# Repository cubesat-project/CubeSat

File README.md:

Check out the Wiki for Project Information

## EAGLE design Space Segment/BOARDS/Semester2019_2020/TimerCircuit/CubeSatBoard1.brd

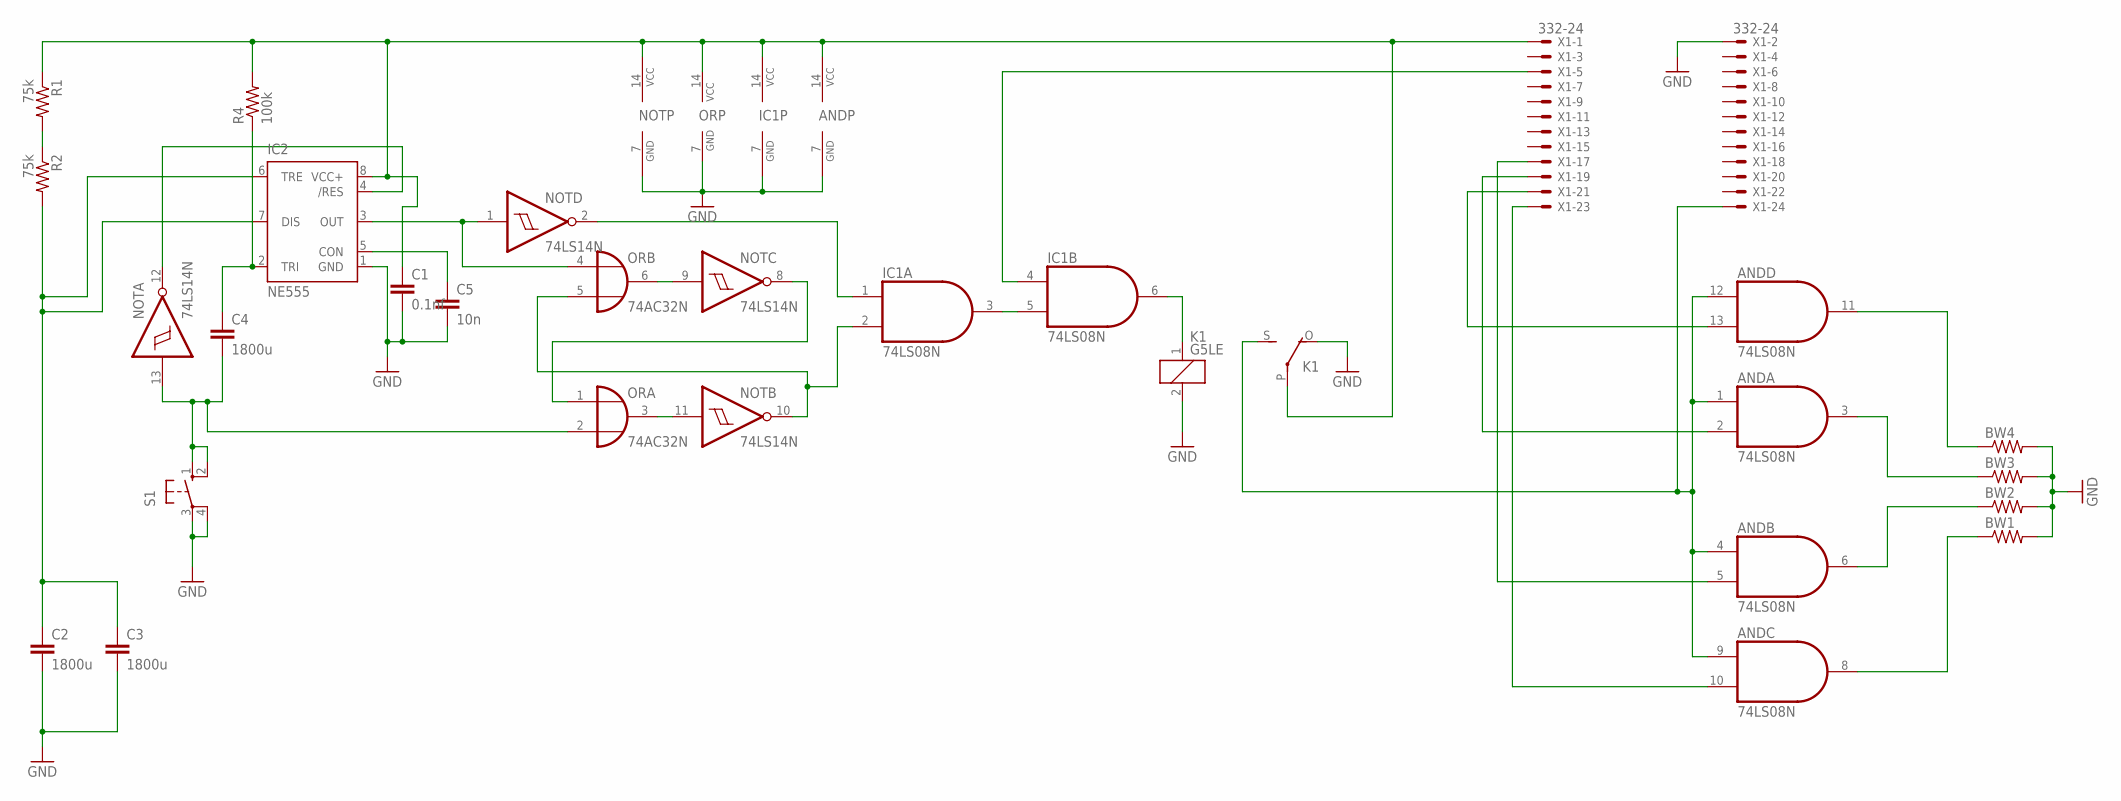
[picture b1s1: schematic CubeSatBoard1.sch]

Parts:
AND: 74LS08N; DIL14
BW1, BW2, BW3, BW4: R-US_0309/10; 0309/10
C1: 0.1nf; C5B3
C2, C3, C4: 1800u; C5B3
C5: 10n; C5B3
IC1: 74LS08N; DIL14
IC2: NE555; DIL-08
K1: G5LE
NOT: 74LS14N; DIL14
OR: 74AC32N; DIL14
R1, R2: 75k; 0309/10
R4: 100k; 0309/10
S1: 10-XX; B3F-10XX
X1: 332-24

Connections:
GND: AND.7 (GND), BW1.2, BW2.2, BW3.2, BW4.2, C1.2, C2.2, C3.2, C5.2, IC1.7 (GND), IC2.1 (GND), K1.2, K1.O, NOT.7 (GND), OR.7 (GND), S1.3, S1.4 (P1), X1.2
unnamed: R1.2, R2.1
unnamed: C2.1, C3.1, IC2.6 (TRE), IC2.7 (DIS), R2.2
unnamed: AND.14 (VCC), C1.1, IC1.14 (VCC), IC2.8 (VCC+), K1.P, NOT.14 (VCC), OR.14 (VCC), R1.1, R4.2, X1.1
unnamed: NOT.9 (I), OR.6 (O)
unnamed: IC2.4 (/RES), NOT.12 (O)
unnamed: NOT.11 (I), OR.3 (O)
unnamed: C4.2, NOT.13 (I), OR.2 (I1), S1.1 (S), S1.2 (S1)
unnamed: C4.1, IC2.2 (TRI), R4.1
unnamed: IC2.3 (OUT), NOT.1 (I), OR.4 (I0)
unnamed: C5.1, IC2.5 (CON)
unnamed: AND.13 (I1), X1.21
unnamed: NOT.8 (O), OR.1 (I0)
unnamed: IC1.2 (I1), NOT.10 (O), OR.5 (I1)
unnamed: IC1.1 (I0), NOT.2 (O)
unnamed: IC1.3 (O), IC1.5 (I1)
unnamed: AND.6 (O), BW2.1
unnamed: IC1.6 (O), K1.1
unnamed: AND.11 (O), BW4.1
unnamed: AND.3 (O), BW3.1
unnamed: AND.8 (O), BW1.1
unnamed: AND.1 (I0), AND.4 (I0), AND.9 (I0), AND.12 (I0), K1.S, X1.24
unnamed: IC1.4 (I0), X1.5
unnamed: AND.2 (I1), X1.19
unnamed: AND.5 (I1), X1.17
unnamed: AND.10 (I1), X1.23

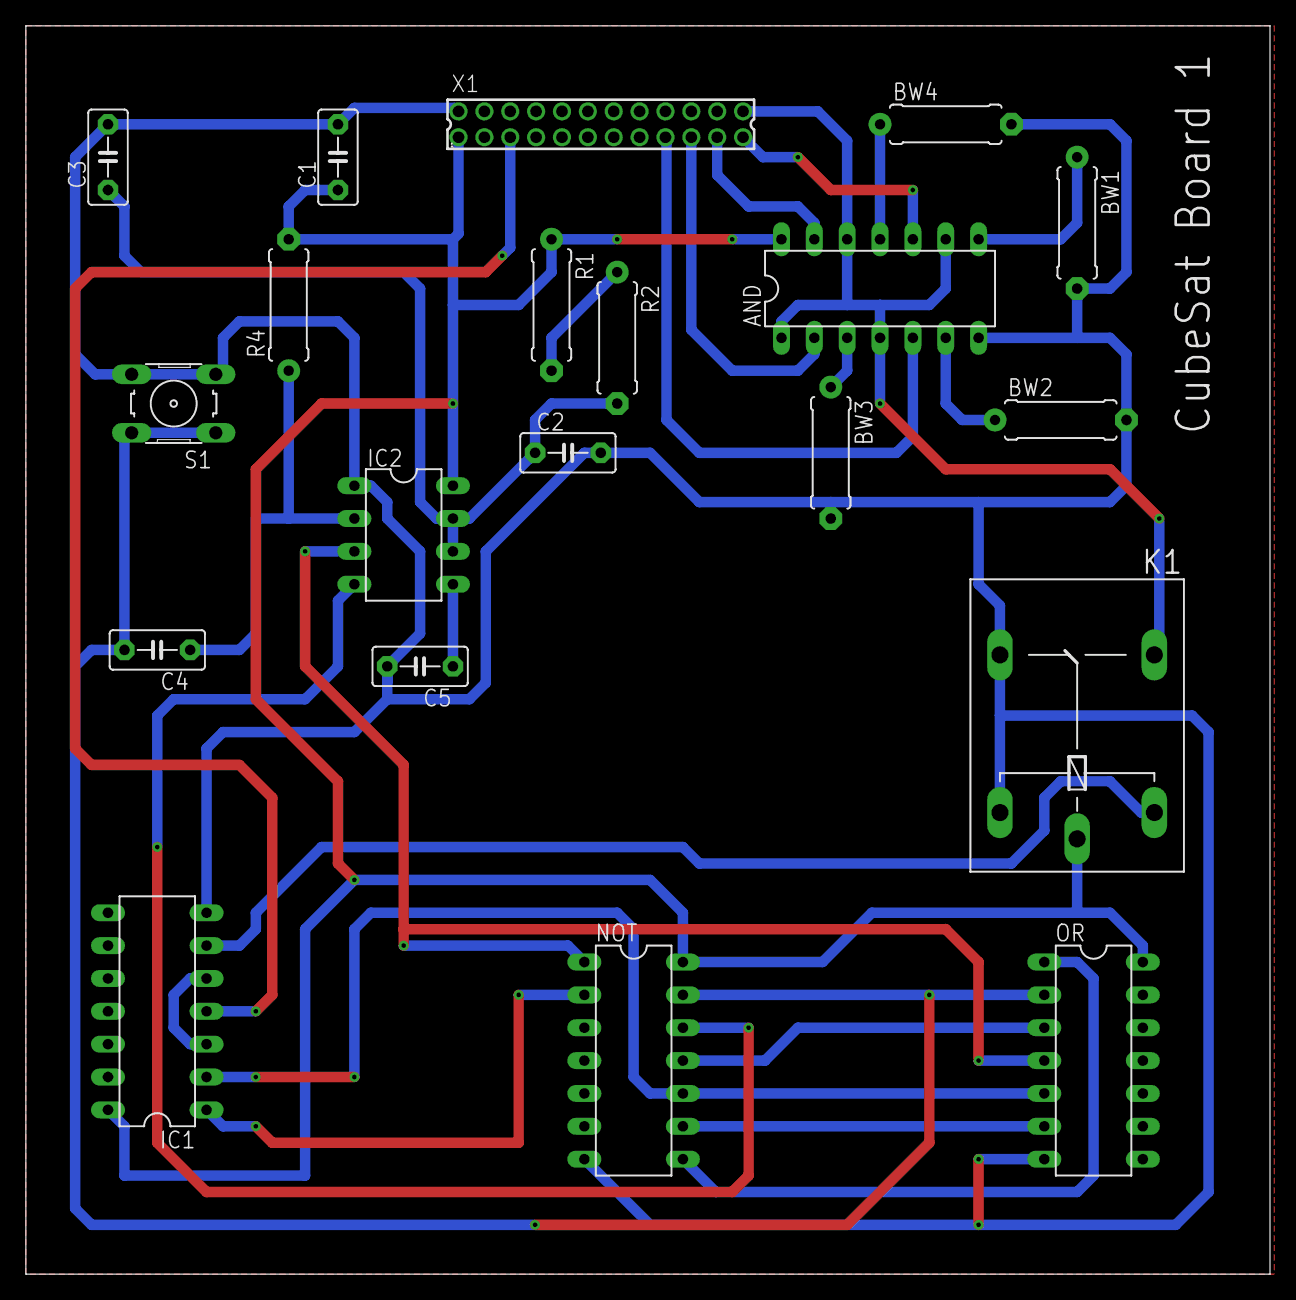
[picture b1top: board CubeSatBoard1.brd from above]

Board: 2 copper layers, 96.2 x 96.5 mm, 20 parts (0 on the bottom side), 26 nets.

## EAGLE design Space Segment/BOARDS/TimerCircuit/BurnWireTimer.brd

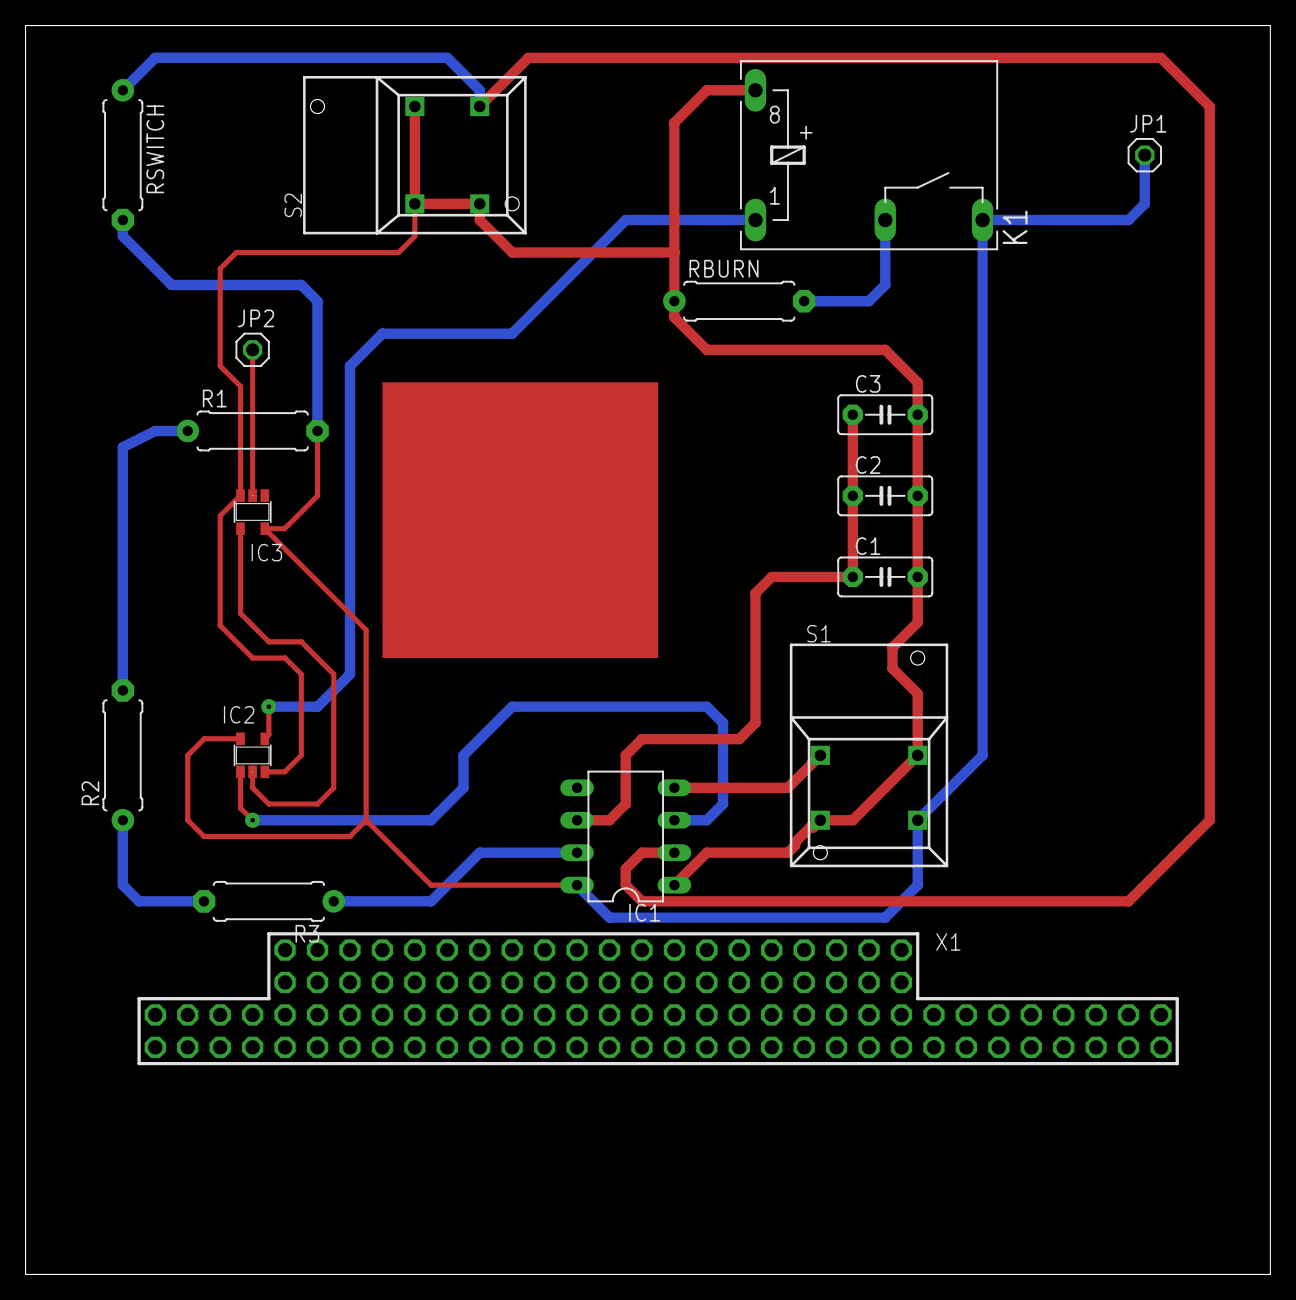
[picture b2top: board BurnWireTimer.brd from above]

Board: 2 copper layers, 97.5 x 97.8 mm, 17 parts (0 on the bottom side), 12 nets.

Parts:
C1, C2, C3: 1800u; C5B3
IC1: ICM7555; DIL08
IC2: 74AHC1G02DBV; SOT23-5
IC3: 74AHC1G04DBV; SOT23-5
JP1: 5V; 1X01
JP2: 1X01
K1: G6C-1117P
R1, R2: 132k; 0309/10
R3: 73k; 0309/10
RBURN: 4.7; 0309/10
RSWITCH: 10k; 0309/10
S1, S2: 5501
X1: 1184C

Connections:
GND: C1.2, C2.2, C3.2, IC1.1, IC2.3, IC3.3, K1.8, RBURN.1, S1.1A, S1.NC, S2.1A, S2.1B, S2.NC
unnamed: IC2.4, K1.1
unnamed: R1.1, R2.2
unnamed: R2.1, R3.2
unnamed: C1.1, C2.1, C3.1, IC1.6, IC1.7, R3.1
unnamed: IC1.4, S1.1B
unnamed: IC1.2, RSWITCH.1, S2.NO
unnamed: IC1.3, IC2.1
unnamed: IC2.2, IC3.4
unnamed: K1.P, RBURN.2
OBC: IC3.2, JP2.1
VCC: IC1.8, IC2.5, IC3.5, JP1.1, K1.S, R1.2, RSWITCH.2, S1.NO

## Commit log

2018-10-15 Create Spacecraft_ICD_Basic_Template
    Copy template and replace 'Template' with name with your spacecraft subsystem.
2018-10-18 Add files via upload
    Working Power Budget for Opportunity
2018-10-28 EPS Opportunity Flow Chart
2018-11-02 Update ADCS/Spacecraft_ICD_Basic_Template
2018-11-02 Organizational Restructuring
2018-11-02 Update Spacecraft_ICD_Basic_Template
    Duplicate, not needed
2018-11-05 Update Spacecraft_ICD_Basic_Template
2018-11-06 Add files via upload
    Reference Coordinate system for Spirit 2U.
2018-11-06 Add files via upload
    Mass budget and other info
2018-11-07 Added file to create folder
    Ignore this template; just needed to added a file for the folder to appear
2018-11-19 Spirit EPS Presentation
    Contains EPS design component ideas with links to their specs. Updated power budget and power models included.
2018-11-23 Add files via upload
    This is the a datasheet for the patch antenna we are currently rolling with.
2019-01-17 Endurosat OBC Datasheet
2019-01-18 Prototype BOM
2019-03-28 Adding Phase 1 code
2019-03-29 MC: removed private environment variables
2019-04-10 Add files via upload
    python code, Arduino code
2019-04-27 Test
2019-04-27 Update Specification Design IMG
2019-04-27 Create Images
2019-04-27 Create ...
2019-04-27 Create Detailed Design
2019-04-27 Create Specification Design
2019-04-27 Create Conceptual Design
2019-04-27 Create Prototype Design
2019-04-27 Create Final Design
2019-05-01 Added capstone reports
2019-06-14 Orbit analysis
2019-08-24 Solar panels Summer Work
2019-08-27 All Orbit Stuff by Danlei
2019-08-27 Removed Danlei Stuff by Request from Danlei cuz more information has been provided
2019-09-23 Nick Work Summer 2019
2019-10-01 nick upload
2019-10-25 Edited By Nick and Chimira :)
2019-10-25 Edits By Nick and Chimira
2019-10-25 Uploaded by ruhmaa
2019-10-30 Edits By Nick
2019-10-31 Edits By Nick Mitchell
2019-10-31 nick Edits
2019-11-05 Nick Edit
2019-11-06 Flight software proposal
    Its a bit outdated now -- GPS removed, other changes. Walk-through presentation report will contain updated info
2019-11-13 Software use-cases
    Use cases for commands may be added/removed/changed at a later date if required
2019-11-22 Added phase 1 report from ADCS
2019-11-28 Create TimerCircuit
2019-11-28 Create testfile
2019-12-02 final draft uploaded by ruhmaa
2019-12-05 Nick Edits post PDR
2019-12-05 Nick Edits PDR
2019-12-06 Edits by Nick after Club meeting
2020-01-13 added by ruhmaa
2020-01-14 Add files via upload
    Equations from Link Budget
2020-01-14 Add files via upload
    SAT COMM 101 Notes from Video
2020-01-22 final draft-rb
2020-01-31 Club Opportunites
2020-02-07 Create TunaCanExtension
2020-02-21 Nick Edits for Nanoracks Safety Data Package
2020-02-21 Nick Edits for Nanoracks safety data pacakge
2020-02-21 Nick Updates
2020-02-21 Nick Edits Nanoracks Safety Data Pacakage
2020-05-29 Adding environment files for ground station
2020-06-03 Software documents
2020-06-23 Add files via upload
    Block Diagram from PDR of the groundStation, uploaded in order to link to IARU frequency coordination request.
2020-06-23 Adding docs for using the Nucleo dev board
2020-06-23 Add files via upload
    general description of ground station software for the purposes of including inside IARU Frequency Coordination Request Form.
2020-06-24 Update Comms Software General Description.docx
    Updated version of document with Stop Communication Command explained
2020-06-24 subcatagorized in IARU frequency coordination folder
2020-06-24 decided the comms software general description and readMe belong in main folder and only the pictures should be in a sub folder
2020-06-25 added questions to ask folder
    added questions for vidushi and question for endurosat files in new folder for questions that will be inquired upon.
2020-06-25 Nick edits on IARU and command docs
2020-06-26 Nick Board edits for Structural meeting
2020-06-29 nick edits and additions
2020-07-11 Add node modules, environment.ts, and node-sass
2020-07-11 package.json
2020-07-11 Completely Updated to Angular v8. Added paths and modified target in tsconfig.json
2020-07-11 Commented out AutguardService for demo
2020-07-11 update @angular/cdk
2020-07-11 Updated Dependencies
2020-07-15 Completely Updated to Angular 9
2020-07-16 Init power analysis over 1.5 months of orbits
2020-07-16 Ways to collect sun-vector data w/ matlab script
2020-07-20 Uploaded templates
2020-07-21 Correctly account for eclipse, beta angles
2020-07-23 Jill Edits Pre-CDR
2020-08-11 fixed comment error
2020-08-12 Added list of CubeSat commands, payload formats
    Added document specifying the byte-oriented payloads for each CubeSat command
2020-08-18 Fixed errors + added comments to power notebook
2020-08-20 Updated parts list for solar panels
    Still missing/unsure about some components - release mount, burnwire, antenna release switch, RBF. Some components have also been removed, e.g. temperature sensors, the photodiode stuff.
2020-08-20 Updated solar panel components list
    Still missing/unsure about some components - release mount, burnwire, antenna release switch, RBF. Some components have also been removed, e.g. temperature sensors, the photodiode stuff.
2020-08-20 Fixed mistakes in parts list file
2020-09-07 nick edits to organize better
2020-10-05 Nick Edits Pre CDR
2020-10-09 Nick Edits for Capstone 2020-2021
2020-10-15 Nick edits !
2021-03-31 nick edits IARU
2022-05-11 Create sample
2022-06-06 COMMS -- GS 2019/. UHF-LinkBudget-Western
    Static file - uploaded 06-06-2022
2022-06-06 Create Link Budget
    Mackenzie edits
2022-06-06 Mackenzie Edits
2022-06-06 Static file
    Uploaded 06-06-2022
2022-06-06 Mackenzie upload
2022-06-06 Create folder
2022-06-08 Create Wiki Images
2022-06-08 create images folder
2022-06-09 Create Blank
2022-06-09 Add files via upload
    Iteration 1 from Kelsey Doerksen, previous student at Western
2022-07-06 Create Empty
2022-07-06 Add files via upload
    Updated July 7th, includes modulation scheme update
2022-07-06 Delete UHF-LinkBudget-Western (1).xlsx
    Old version

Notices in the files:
parts and their libraries:
con-pc104: Copyright 1992-96, PC/104 Consortium
Copyright 1992-98, PC/104 Consortium
